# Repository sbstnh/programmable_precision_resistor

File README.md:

# Programmable Precision Resistor

A SCPI programmable precision resistor

**WARNING:** The programmable power resistor presented is mains powered. On the power supply board there will be mains/line voltage. Working with/on such devices can lead to damage, injury or death. Don't do it if you're not qualified or authorized to do so. You use the circuits described at you own risk. You have to make sure that the circuit is safe and adheres to the applicable standards in your location. You might operate the mainboard and ui board more safely with a bench or external power supply.

**WARNING:** I abandoned the AC/DC converter of the initial design mostly due to EMI issues. I ended up using a EI-core (isolation) transformer, bridge rectifier, capacitor two tiny DC/DC converters. Some of the documentation does not reflect this change.

## Background and motivation

In 2021/2022 I designed a DC electronic load that would be more capable, but also much more complex than the usual DIY solutions. However, after building a working breadboard prototype of the analog circuitry with 12 ICs including multiple precision and dual opamps, I thought that it might be better to start with a smaller project that would allow me to gain a lot of experience and write much of the non-application specific code that I could use later on for the digital part. Also, at the time I was looking for a decade resistor box to add to my lab. And this is how I started working on a programmable decade resistor, a pretty specialized tool for niche applications.

## Introduction

A programmable resistor is a electronic device whose electrical resistance can be adjusted typically through digital signals. Programmable resistors are available in form of integrated circuits (often referred to as digital potentiometers) as well as stand-alone devices/expansion cards. There are many different applications, each with their own set of requirements e. g.:

programmable gain amplifiers
sensor emulation, e. g. for integration tests with hardware-in-the-loop simulators
automated testing
calibrators
prototyping
Basic concept
The programmable resistor closely follows the main principle of resistor decade boxes: connecting multiple devices (“decades”) in series, with each of the devices having a settable resistance of 0 Ω, 1 ⋅ 10^n Ω, 2 ⋅ 10^n Ω, 9 ⋅ 10^n Ω, where n specifies the decade in question.

Those devices are simple resistor networks complemented by one (multi-throw) or more (single- or multi-throw) switches. While the actual topology and resistor values vary vastly, the switch(es) will always either short out or connect certain resistors or simply tap certain nodes of the resistor network. A simple implementation uses a 10-throw rotary switch to tap the nodes of a series resistor network of nine resistors.

## Features

| Parameter                                | Value / Description                                                                                                                                                                                                                                                                                                                                                                                                                                       |
| :--------------------------------------- | :-------------------------------------------------------------------------------------------------------------------------------------------------------------------------------------------------------------------------------------------------------------------------------------------------------------------------------------------------------------------------------------------------------------------------------------------------------- |
| Range                                    | short circuit, 1 Ω … 999.999 kΩ, open circuit                                                                                                                                                                                                                                                                                                                                                                                                          |
| Setpoint resolution                      | 1 Ω                                                                                                                                                                                                                                                                                                                                                                                                                                                      |
| Short-term setpoint accuracy estimate    | <=±0.1% of value + 0.15 Ω (2W and 4W). The estimate is based on measurements for a limited number of calibration and validation resistance setpoints. The measurements were performed with an older Agilent 34401A 6.5 digit multimeter for a single DUT. This is NOT a valid strategy to get reliable/reproducible results in the sense of a specification. It's just a more or less plausible envelope based on measurements I took for my prototype. |
| Display value resolution                 | 6.5 digits, 5.5 digits, 4.5 digits, 3.5 digits, but not better than 1 mΩ                                                                                                                                                                                                                                                                                                                                                                                 |
| Short-term display accuracy estimate     | <=±0.01% + 0.025 Ω (2W and 4W). This figure is meant to show how much the displayed resistance value (that is based on a calibration) deviates from the value shown on the DMM, the calibration has been performed with.                                                                                                                                                                                                                                |
| Thermal drift (estimate based on design) | <<50 ppm/K                                                                                                                                                                                                                                                                                                                                                                                                                                                |
| Power rating                             | >=0.2W for decade 0 (0..9Ω),<br />>=0.5W else<br />Exact value depends on setpoint (display)                                                                                                                                                                                                                                                                                                                                                             |
| Bandwidth                                | unspecified                                                                                                                                                                                                                                                                                                                                                                                                                                               |
| Calibration modes                        | - Uncalibrated: Switches are activated according to entered setpoint, display shows setpoint<br />- Two-wire (2W), Four-wire (4W): An internal setpoint is calculated based on the calibration values to reduce the error (effects changes for higher resistance values only)                                                                                                                                                                             |
| Operating modes                          | Fixed: On trigger no change<br />Step: On trigger step to trigger setpoint value<br />Up: On trigger increase setpoint (linearly, 1-2-3-4-5-6-7-8-9, 1-2-5, 1-3)<br />Down: On trigger increase setpoint (linearly, 1-2-3-4-5-6-7-8-9, 1-2-5, 1-3)<br />List: See list mode                                                                                                                                                                               |
| List mode                                | Up to 100 values with individual dwell times<br />- Start: on trigger; or immediately after mode selection<br />- Step:<br />  - Auto: Advance index automatically, solely based on dwell time<br />  - Trigger: Advance index on each trigger event, ignoring the dwell time<br />  - Once: Advance index on each trigger event, only after dwell time elapsed                                                                                           |
| Switching                                | fast (default), break-before-make                                                                                                                                                                                                                                                                                                                                                                                                                         |
| Trigger                                  | Source: Bus, External (Rising, Falling, Either), Immediate, Manual, Timer;<br />Mode: Continuous, Single<br />Parameter: Delay, Holdoff, Time (Source: Timer)                                                                                                                                                                                                                                                                                             |
| Inhibit                                  | Inhibit the input<br />- Latching: Latch input on/off on inhibit input change<br />- Live: Switch input on/off according to present inhibit input state                                                                                                                                                                                                                                                                                                   |
| Command and trigger execution            | 10ms loops                                                                                                                                                                                                                                                                                                                                                                                                                                                |
| User interface                           | - 18 digit alphanumeric display:<br />  - Primary display: Resistance setpoint<br />  - Secondary display: Input state, max. current at setpoint, max. voltage at setpoint, max. power at setpoint, hardware setpoint<br />  - Menu-based<br />- 6 dual color LEDs<br />- Rotary encoder with push button<br />- 23 additional push buttons                                                                                                               |
| User presets                             | 0-9; 0 is loaded on power-up                                                                                                                                                                                                                                                                                                                                                                                                                              |
| Interface                                | - USB<br />- Two digital inputs, settable polarity (positive, negative) and function (trigger, inhibit, readout)                                                                                                                                                                                                                                                                                                                                          |
| Power supply                             | Switch mode                                                                                                                                                                                                                                                                                                                                                                                                                                               |

## System design

The block diagram provides an overview of the different circuit groups of each functional block, their internal connections and external interfaces. The Programmable Decade Resistor consists of three main functional blocks:

1. Power supply (Power Supply Board), an external EMI filter is required.
2. Programmable decades, control and driver circuits (Mainboard)
3. User Interface (User Interface Board)

The power supply board uses an off-the-shelve AC/DC converter to provide a +15V rail. The +15V rail powers the relays on the mainboard as well as a DC/DC converter. A single DC/DC converter generates a +3.3V supply for both the mainboard and the UI board, including the LED display. The power rails are earth-referenced. (Nevertheless, the inputs of the Programmable Decade Resistor are floating thanks to the isolation of the relays.)

The mainboard’s main controller contains the business logic to control the relays, read the external inputs and run the USB and user interfaces. The main controller communicates with the User Interface Board over I2C which handles the multiplexing of the alphanumeric LED display, scans the switch matrix, decodes the signals of the rotary encoder and drives the buzzer.

Note that these pictures DO NOT represent the final design of the Programmable Precision Resistor and the power supply circuit in particular.

## Results

After the final calibration the results are in. The first diagram shows the absolute value of the deviation between the setpoint and the value indicated by the Agilent 34401A multimeter. Connecting lines between data points for visual purposes only.

The second diagram shows the absolute value of the deviation between the calculated resistance (estimate based on calibration values) and the value indicated by the Agilent 34401A multimeter. Connecting lines between data points for visual purposes only

## About this repository

This repository contains the PCB design files used in this project. If you'd like to have a look at the interactive bom files you can do so here:

- Mainboard: [HTML Preview of interactive BOM](https://htmlpreview.github.io/?https://github.com/sbstnh/programmable_precision_resistor/blob/main/pcb/mainboard/bom/ibom.html)
- UI board: [HTML Preview of interactive BOM](https://htmlpreview.github.io/?https://github.com/sbstnh/programmable_precision_resistor/blob/main/pcb/ui_board/bom/ibom.html)
- Power Supply Board: [HTML Preview of interactive BOM](https://htmlpreview.github.io/?https://github.com/sbstnh/programmable_precision_resistor/blob/main/pcb/power_supply/bom/ibom.html)

## Further information

More details are available at [https://hackaday.io/project/191969-programmable-precision-resistor](https://hackaday.io/project/191969-programmable-precision-resistor) and on my personal site [https://sebastianharnisch.de](https://sebastianharnisch.de).

## Firmware and License

The firmware was created with STM32CubeIDE and uses code auto-generated by or provided with the IDE, including
- the HAL library, code related to the USB device and other code
- FreeRTOS

Further more, this project uses a SCPI parser library that can be found here: [https://github.com/j123b567/scpi-parser](https://github.com/j123b567/scpi-parser)

Most of the auto-generated code as well as the libraries are not included here.
Therefore it is recommended to use STM32CubeIDE to create a project for the target device, with the USB device software and FreeRTOS enabled, add the required SCPI library and adapt the code according to the requirements.

For the code not included in this repository the respective licenses will apply instead of the license specified in this repository.

I DO NOT guarantee that the code provided is free of bugs (see LICENSE file for more details).

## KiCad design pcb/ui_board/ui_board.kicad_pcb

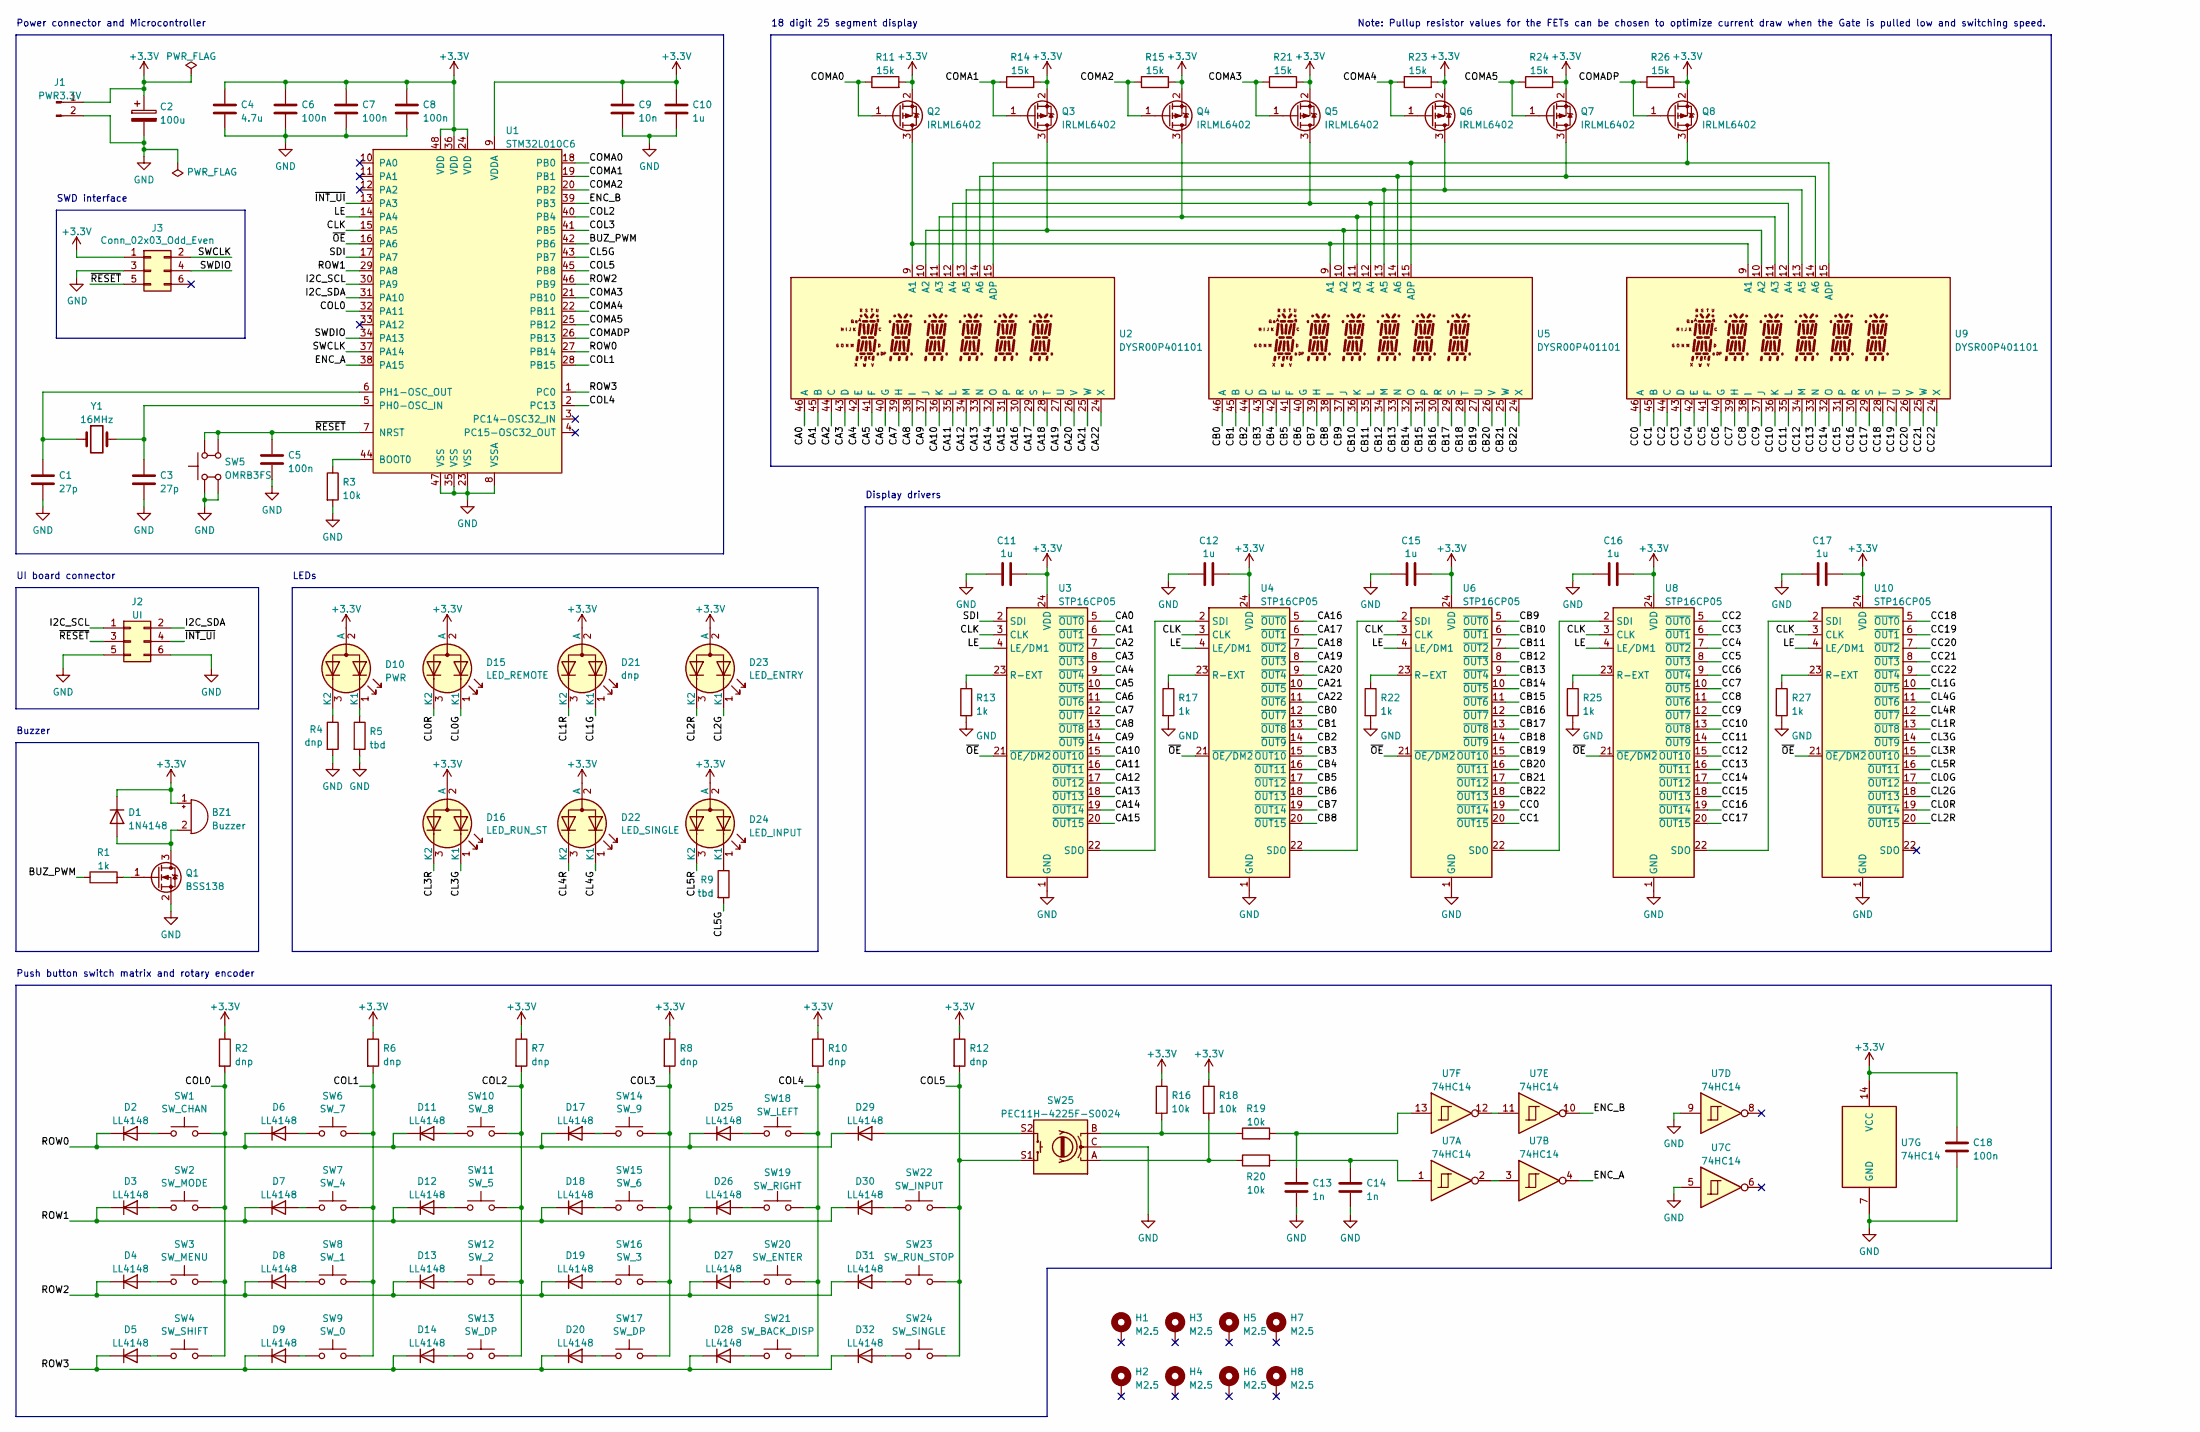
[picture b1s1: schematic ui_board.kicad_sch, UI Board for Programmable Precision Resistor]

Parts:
BZ1: Buzzer; Buzzer_Ekulit_AL-60P06_D12mm_H9mm
C1, C3: 27p; C_0603_1608Metric_Box
C2: 100u; CP_EIA-7343-31_Kemet-D_Pad2.25x2.55mm_HandSolder
C4: 4.7u; C_0603_1608Metric_Box
C5, C6, C7, C8, C18: 100n; C_0603_1608Metric_Box
C9: 10n; C_0603_1608Metric_Box
C10, C11, C12, C15, C16, C17: 1u; C_0603_1608Metric_Box
C13, C14: 1n; C_0603_1608Metric_Box
D1: 1N4148; D_MiniMELF
D2, D3, D4, D5, D6, D7, D8, D9, D11, D12, D13, D14, D17, D18, D19, D20, D25, D26, D27, D28, D29, D30, D31, D32: LL4148; D_MiniMELF
D10: PWR; LED_D3.0mm-3
D15: LED_REMOTE; LED_D3.0mm-3
D16: LED_RUN_ST; LED_D3.0mm-3
D21: dnp; LED_D3.0mm-3
D22: LED_SINGLE; LED_D3.0mm-3
D23: LED_ENTRY; LED_D3.0mm-3
D24: LED_INPUT; LED_D3.0mm-3
H1, H2, H3, H4, H5, H6, H7, H8: M2.5; MountingHole_2.7mm_M2.5_DIN965_Pad
J1: PWR3.3V; Molex_KK-254_AE-6410-02A_1x02_P2.54mm_Vertical
J2: UI; PinHeader_2x03_P2.54mm_Vertical
J3: Conn_02x03_Odd_Even; PinHeader_2x03_P2.54mm_Vertical
Q1: BSS138; SOT-23
Q2, Q3, Q4, Q5, Q6, Q7, Q8: IRLML6402; SOT-23
R1: 1k; R_0805_2012Metric_Box
R2, R4, R6, R7, R8, R10, R12: dnp; R_0603_1608Metric_Box
R3, R16, R18, R19, R20: 10k; R_0603_1608Metric_Box
R5, R9: tbd; R_0603_1608Metric_Box
R11, R14, R15, R21, R23, R24, R26: 15k; R_0603_1608Metric_Box
R13, R17, R22, R25, R27: 1k; R_0603_1608Metric_Box
SW1: SW_CHAN; PVA1
SW2: SW_MODE; PVA1
SW3: SW_MENU; PVA1
SW4: SW_SHIFT; PVA1
SW5: OMRB3FS; OMR_B3FS
SW6: SW_7; PVA1
SW7: SW_4; PVA1
SW8: SW_1; PVA1
SW9: SW_0; PVA1
SW10: SW_8; PVA1
SW11: SW_5; PVA1
SW12: SW_2; PVA1
SW13, SW17: SW_DP; PVA1
SW14: SW_9; PVA1
SW15: SW_6; PVA1
SW16: SW_3; PVA1
SW18: SW_LEFT; PVA1
SW19: SW_RIGHT; PVA1
SW20: SW_ENTER; PVA1
SW21: SW_BACK_DISP; PVA1
SW22: SW_INPUT; PVA1
SW23: SW_RUN_STOP; PVA1
SW24: SW_SINGLE; PVA1
SW25: PEC11H-4225F-S0024; RotaryEncoder_Alps_EC11E-Switch_Vertical_H20mm_CircularMoun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
U1: STM32L010C6; LQFP-48_7x7mm_P0.5mm
U2, U5, U9: DYSR00P401101
U3, U4, U6, U8, U10: STP16CP05; TSSOP-24_4.4x7.8mm_P0.65mm
U7: 74HC14; SO-14_3.9x8.65mm_P1.27mm
Y1: 16MHz; Crystal_HC49-4H_Vertical

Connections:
+3.3V: BZ1.1 (-), C2.1, C4.1, C6.1, C7.1, C8.1, C9.1, C10.1, C11.1, C12.1, C15.1, C16.1, C17.1, C18.1, D1.1 (K), D10.2 (A), D15.2 (A), D16.2 (A), D21.2 (A), D22.2 (A), D23.2 (A), D24.2 (A), J1.1, J3.1, Q2.2 (S), Q3.2 (S), Q4.2 (S), Q5.2 (S), Q6.2 (S), Q7.2 (S), Q8.2 (S), R2.1, R6.1, R7.1, R8.1, R10.1, R11.2, R12.1, R14.2, R15.2, R16.1, R18.1, R21.2, R23.2, R24.2, R26.2, U1.9 (VDDA), U1.24 (VDD), U1.36 (VDD), U1.48 (VDD), U3.24 (VDD), U4.24 (VDD), U6.24 (VDD), U7.14 (VCC), U8.24 (VDD), U10.24 (VDD)
/BUZ_PWM: R1.1, U1.42 (PB6)
/CA0: U2.46 (A), U3.5 (~OUT0)
/CA1: U2.45 (B), U3.6 (~OUT1)
/CA2: U2.44 (C), U3.7 (~OUT2)
/CA3: U2.43 (D), U3.8 (~OUT3)
/CA4: U2.42 (E), U3.9 (~OUT4)
/CA5: U2.41 (F), U3.10 (~OUT5)
/CA6: U2.40 (G), U3.11 (~OUT6)
/CA7: U2.39 (H), U3.12 (~OUT7)
/CA8: U2.38 (I), U3.13 (~OUT8)
/CA9: U2.37 (J), U3.14 (~OUT9)
/CA10: U2.36 (K), U3.15 (~OUT10)
/CA11: U2.35 (L), U3.16 (~OUT11)
/CA12: U2.34 (M), U3.17 (~OUT12)
/CA13: U2.33 (N), U3.18 (~OUT13)
/CA14: U2.32 (O), U3.19 (~OUT14)
/CA15: U2.31, U3.20 (~OUT15)
/CA16: U2.30 (R), U4.5 (~OUT0)
/CA17: U2.29 (S), U4.6 (~OUT1)
/CA18: U2.28 (T), U4.7 (~OUT2)
/CA19: U2.27 (U), U4.8 (~OUT3)
/CA20: U2.26 (V), U4.9 (~OUT4)
/CA21: U2.25 (W), U4.10 (~OUT5)
/CA22: U2.24 (X), U4.11 (~OUT6)
/CB0: U4.12 (~OUT7), U5.46 (A)
/CB1: U4.13 (~OUT8), U5.45 (B)
/CB2: U4.14 (~OUT9), U5.44 (C)
/CB3: U4.15 (~OUT10), U5.43 (D)
/CB4: U4.16 (~OUT11), U5.42 (E)
/CB5: U4.17 (~OUT12), U5.41 (F)
/CB6: U4.18 (~OUT13), U5.40 (G)
/CB7: U4.19 (~OUT14), U5.39 (H)
/CB8: U4.20 (~OUT15), U5.38 (I)
/CB9: U5.37 (J), U6.5 (~OUT0)
/CB10: U5.36 (K), U6.6 (~OUT1)
/CB11: U5.35 (L), U6.7 (~OUT2)
/CB12: U5.34 (M), U6.8 (~OUT3)
/CB13: U5.33 (N), U6.9 (~OUT4)
/CB14: U5.32 (O), U6.10 (~OUT5)
/CB15: U5.31, U6.11 (~OUT6)
/CB16: U5.30 (R), U6.12 (~OUT7)
/CB17: U5.29 (S), U6.13 (~OUT8)
/CB18: U5.28 (T), U6.14 (~OUT9)
/CB19: U5.27 (U), U6.15 (~OUT10)
/CB20: U5.26 (V), U6.16 (~OUT11)
/CB21: U5.25 (W), U6.17 (~OUT12)
/CB22: U5.24 (X), U6.18 (~OUT13)
/CC0: U6.19 (~OUT14), U9.46 (A)
/CC1: U6.20 (~OUT15), U9.45 (B)
/CC2: U8.5 (~OUT0), U9.44 (C)
/CC3: U8.6 (~OUT1), U9.43 (D)
/CC4: U8.7 (~OUT2), U9.42 (E)
/CC5: U8.8 (~OUT3), U9.41 (F)
/CC6: U8.9 (~OUT4), U9.40 (G)
/CC7: U8.10 (~OUT5), U9.39 (H)
/CC8: U8.11 (~OUT6), U9.38 (I)
/CC9: U8.12 (~OUT7), U9.37 (J)
/CC10: U8.13 (~OUT8), U9.36 (K)
/CC11: U8.14 (~OUT9), U9.35 (L)
/CC12: U8.15 (~OUT10), U9.34 (M)
/CC13: U8.16 (~OUT11), U9.33 (N)
/CC14: U8.17 (~OUT12), U9.32 (O)
/CC15: U8.18 (~OUT13), U9.31
/CC16: U8.19 (~OUT14), U9.30 (R)
/CC17: U8.20 (~OUT15), U9.29 (S)
/CC18: U9.28 (T), U10.5 (~OUT0)
/CC19: U9.27 (U), U10.6 (~OUT1)
/CC20: U9.26 (V), U10.7 (~OUT2)
/CC21: U9.25 (W), U10.8 (~OUT3)
/CC22: U9.24 (X), U10.9 (~OUT4)
/CL0G: D15.1 (K1), U10.17 (~OUT12)
/CL0R: D15.3 (K2), U10.19 (~OUT14)
/CL1G: D21.1 (K1), U10.10 (~OUT5)
/CL1R: D21.3 (K2), U10.13 (~OUT8)
/CL2G: D23.1 (K1), U10.18 (~OUT13)
/CL2R: D23.3 (K2), U10.20 (~OUT15)
/CL3G: D16.1 (K1), U10.14 (~OUT9)
/CL3R: D16.3 (K2), U10.15 (~OUT10)
/CL4G: D22.1 (K1), U10.11 (~OUT6)
/CL4R: D22.3 (K2), U10.12 (~OUT7)
/CL5G: R9.2, U1.43 (PB7)
/CL5R: D24.3 (K2), U10.16 (~OUT11)
/CLK: U1.15 (PA5), U3.3 (CLK), U4.3 (CLK), U6.3 (CLK), U8.3 (CLK), U10.3 (CLK)
/COL0: R2.2, SW1.2, SW2.2, SW3.2, SW4.2, U1.32 (PA11)
/COL1: R6.2, SW6.2, SW7.2, SW8.2, SW9.2, U1.28 (PB15)
/COL2: R7.2, SW10.2, SW11.2, SW12.2, SW13.2, U1.40 (PB4)
/COL3: R8.2, SW14.2, SW15.2, SW16.2, SW17.2, U1.41 (PB5)
/COL4: R10.2, SW18.2, SW19.2, SW20.2, SW21.2, U1.2 (PC13)
/COL5: R12.2, SW22.2, SW23.2, SW24.2, SW25.S1, U1.45 (PB8)
/COMA0: Q2.1 (G), R11.1, U1.18 (PB0)
/COMA1: Q3.1 (G), R14.1, U1.19 (PB1)
/COMA2: Q4.1 (G), R15.1, U1.20 (PB2)
/COMA3: Q5.1 (G), R21.1, U1.21 (PB10)
/COMA4: Q6.1 (G), R23.1, U1.22 (PB11)
/COMA5: Q7.1 (G), R24.1, U1.25 (PB12)
/COMADP: Q8.1 (G), R26.1, U1.26 (PB13)
/ENC_A: U1.38 (PA15), U7.4
/ENC_B: U1.39 (PB3), U7.10
/I2C_SCL: J2.1, U1.30 (PA9)
/I2C_SDA: J2.2, U1.31 (PA10)
/LE: U1.14 (PA4), U3.4 (LE/DM1), U4.4 (LE/DM1), U6.4 (LE/DM1), U8.4 (LE/DM1), U10.4 (LE/DM1)
/ROW0: D2.1 (K), D6.1 (K), D11.1 (K), D17.1 (K), D25.1 (K), D29.1 (K), U1.27 (PB14)
/ROW1: D3.1 (K), D7.1 (K), D12.1 (K), D18.1 (K), D26.1 (K), D30.1 (K), U1.29 (PA8)
/ROW2: D4.1 (K), D8.1 (K), D13.1 (K), D19.1 (K), D27.1 (K), D31.1 (K), U1.46 (PB9)
/ROW3: D5.1 (K), D9.1 (K), D14.1 (K), D20.1 (K), D28.1 (K), D32.1 (K), U1.1 (PC0)
/SDI: U1.17 (PA7), U3.2 (SDI)
/SWCLK: J3.2, U1.37 (PA14)
/SWDIO: J3.4, U1.34 (PA13)
/~INT_UI: J2.4, U1.13 (PA3)
/~OE: U1.16 (PA6), U3.21 (~OE/DM2), U4.21 (~OE/DM2), U6.21 (~OE/DM2), U8.21 (~OE/DM2), U10.21 (~OE/DM2)
/~RESET: C5.1, J2.3, J3.5, SW5.3, SW5.4, U1.7 (NRST)
GND: C1.2, C2.2, C3.2, C4.2, C5.2, C6.2, C7.2, C8.2, C9.2, C10.2, C11.2, C12.2, C13.2, C14.2, C15.2, C16.2, C17.2, C18.2, J1.2, J2.5, J2.6, J3.3, Q1.2 (S), R3.2, R4.2, R5.2, R13.2, R17.2, R22.2, R25.2, R27.2, SW5.1, SW5.2, SW25.C, U1.8 (VSSA), U1.23 (VSS), U1.35 (VSS), U1.47 (VSS), U3.1 (GND), U4.1 (GND), U6.1 (GND), U7.5, U7.7 (GND), U7.9, U8.1 (GND), U10.1 (GND)
unnamed: BZ1.2 (+), D1.2 (A), Q1.3 (D)
unnamed: C13.1, R19.2, U7.13
unnamed: C14.1, R20.2, U7.1
unnamed: D2.2 (A), SW1.1
unnamed: D3.2 (A), SW2.1
unnamed: D4.2 (A), SW3.1
unnamed: D5.2 (A), SW4.1
unnamed: D6.2 (A), SW6.1
unnamed: D7.2 (A), SW7.1
unnamed: D8.2 (A), SW8.1
unnamed: D9.2 (A), SW9.1
unnamed: D10.1 (K1), R5.1
unnamed: D10.3 (K2), R4.1
unnamed: D11.2 (A), SW10.1
unnamed: D12.2 (A), SW11.1
unnamed: D13.2 (A), SW12.1
unnamed: D14.2 (A), SW13.1
unnamed: D17.2 (A), SW14.1
unnamed: D18.2 (A), SW15.1
unnamed: D19.2 (A), SW16.1
unnamed: D20.2 (A), SW17.1
unnamed: D24.1 (K1), R9.1
unnamed: D25.2 (A), SW18.1
unnamed: D26.2 (A), SW19.1
unnamed: D27.2 (A), SW20.1
unnamed: D28.2 (A), SW21.1
unnamed: D29.2 (A), SW25.S2
unnamed: D30.2 (A), SW22.1
unnamed: D31.2 (A), SW23.1
unnamed: D32.2 (A), SW24.1
unnamed: Q1.1 (G), R1.2
unnamed: Q2.3 (D), U2.9 (A1), U5.9 (A1), U9.9 (A1)
unnamed: Q3.3 (D), U2.10 (A2), U5.10 (A2), U9.10 (A2)
unnamed: Q4.3 (D), U2.11 (A3), U5.11 (A3), U9.11 (A3)
unnamed: Q5.3 (D), U2.12 (A4), U5.12 (A4), U9.12 (A4)
unnamed: Q6.3 (D), U2.13 (A5), U5.13 (A5), U9.13 (A5)
unnamed: Q7.3 (D), U2.14 (A6), U5.14 (A6), U9.14 (A6)
unnamed: Q8.3 (D), U2.15 (ADP), U5.15 (ADP), U9.15 (ADP)
unnamed: R16.2, R19.1, SW25.B
unnamed: R18.2, R20.1, SW25.A
unnamed: R3.1, U1.44 (BOOT0)
unnamed: C3.1, U1.5 (PH0-OSC_IN), Y1.2
unnamed: C1.1, U1.6 (PH1-OSC_OUT), Y1.1
unnamed: R13.1, U3.23 (R-EXT)
unnamed: U3.22 (SDO), U4.2 (SDI)
unnamed: R17.1, U4.23 (R-EXT)
unnamed: U4.22 (SDO), U6.2 (SDI)
unnamed: R22.1, U6.23 (R-EXT)
unnamed: U6.22 (SDO), U8.2 (SDI)
unnamed: U7.2, U7.3
unnamed: U7.11, U7.12
unnamed: R25.1, U8.23 (R-EXT)
unnamed: R27.1, U10.23 (R-EXT)
unnamed: U8.22 (SDO), U10.2 (SDI)

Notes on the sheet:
Push button switch matrix and rotary encoder
Display drivers
18 digit 25 segment display
SWD interface
LEDs
Power connector and Microcontroller
UI board connector
Buzzer
Note: Pullup resistor values for the FETs can be chosen to optimize current draw when the Gate is pulled low and switching speed.

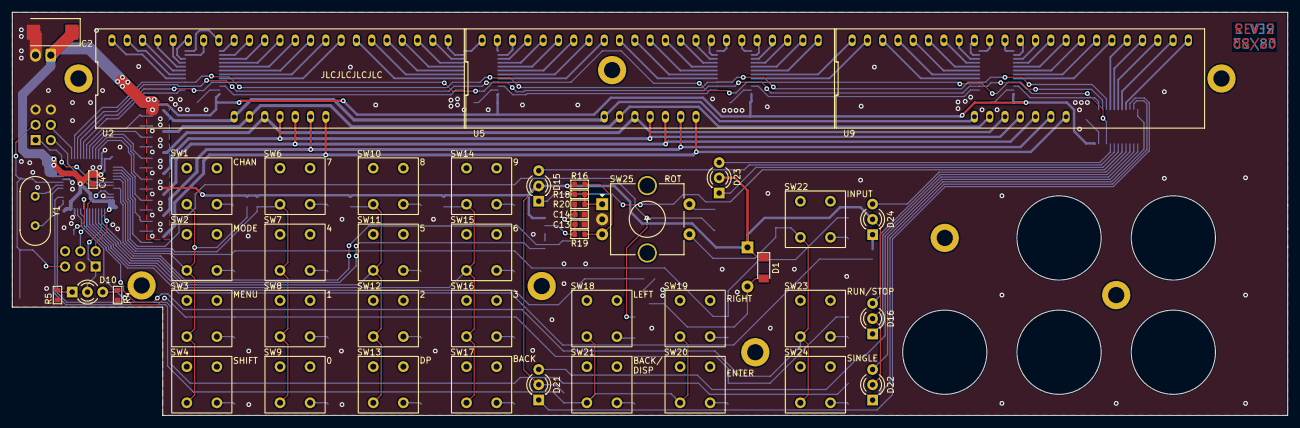
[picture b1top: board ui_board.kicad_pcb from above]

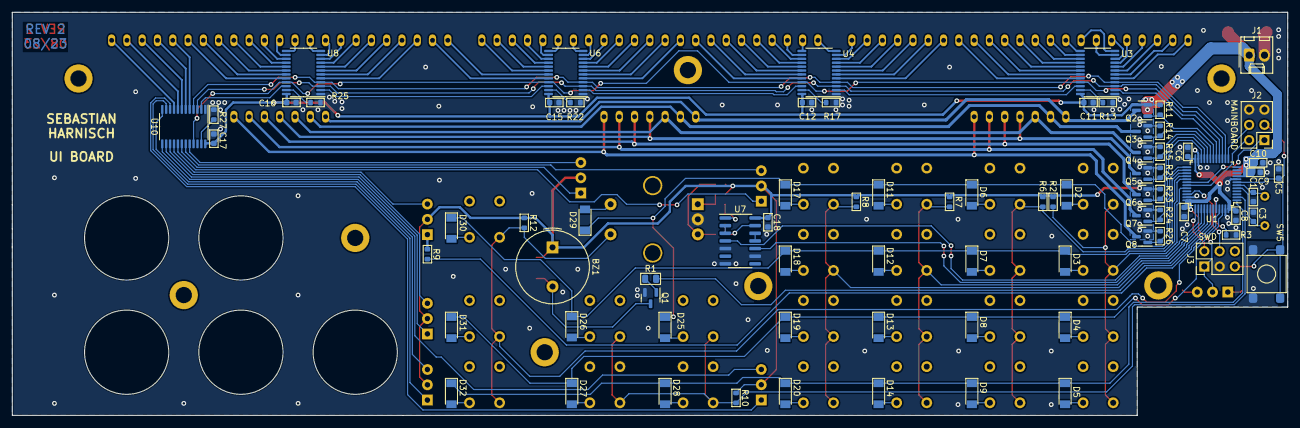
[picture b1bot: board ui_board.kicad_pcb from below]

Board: 2 copper layers, 212.0 x 67.0 mm, 133 parts (79 on the bottom side), 167 nets.

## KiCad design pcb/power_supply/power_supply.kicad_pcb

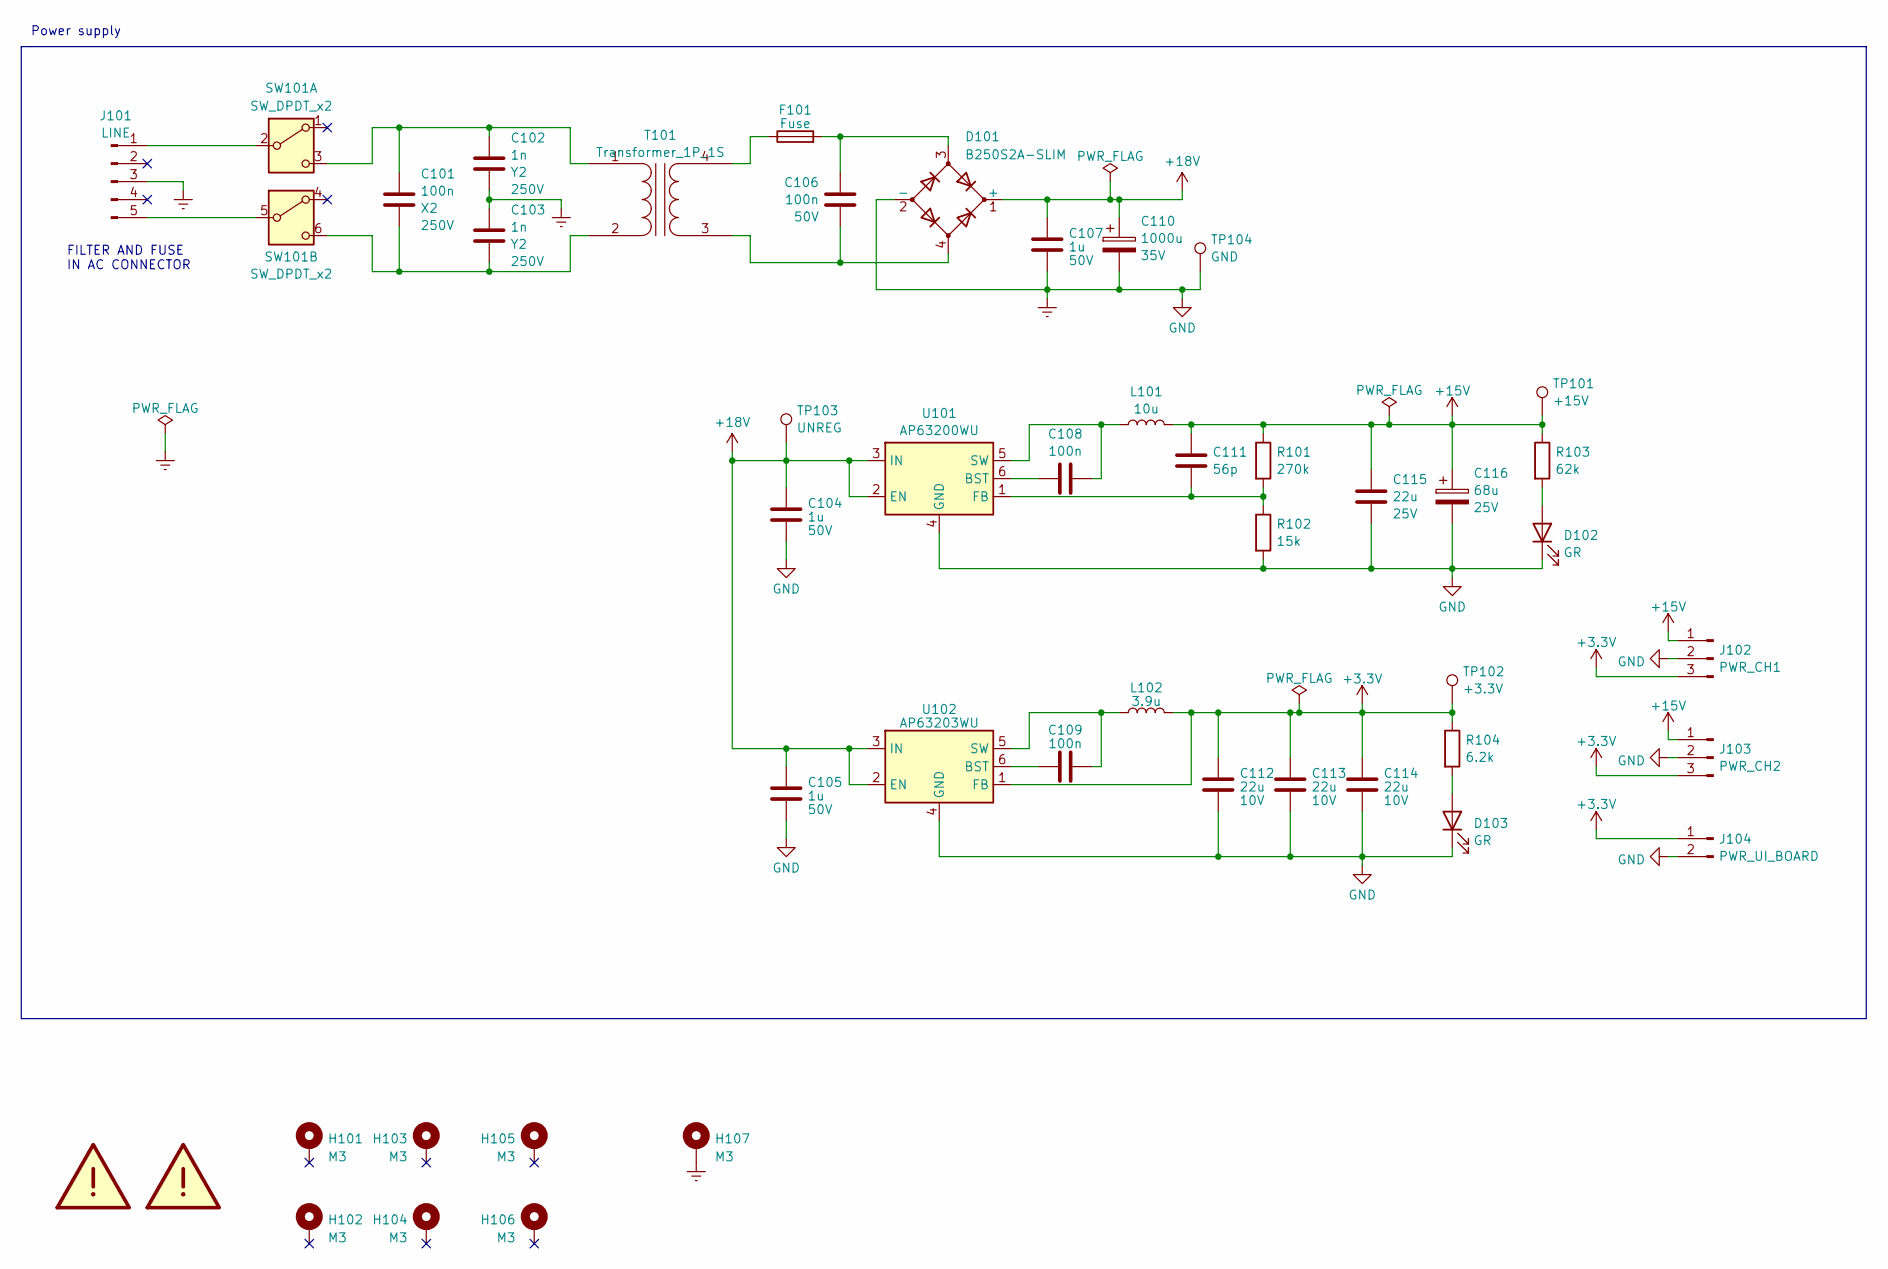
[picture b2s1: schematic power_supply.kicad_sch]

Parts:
C101: 100n; C_Rect_L18.0mm_W5.0mm_P15.00mm_FKS3_FKP3; Voltage Rating 250V
C102, C103: 1n; C_Rect_L13.5mm_W5.0mm_P10.00mm_FKS3_FKP3_MKS4; Voltage Rating 250V
C104, C105: 1u; C_1206_3216Metric; Voltage Rating 50V
C106: 100n; C_0805_2012Metric; Voltage Rating 50V
C107: 1u; C_0805_2012Metric; Voltage Rating 50V
C108, C109: 100n; C_0603_1608Metric
C110: 1000u; CP_Radial_D16.0mm_P7.50mm; Voltage Rating 35V
C111: 56p; C_0603_1608Metric
C112, C113, C114: 22u; C_1206_3216Metric; Voltage Rating 10V
C115: 22u; C_1206_3216Metric; Voltage Rating 25V
C116: 68u; C_Elec_6.3x5.8; Voltage Rating 25V
D101: B250S2A-SLIM; Diode_Bridge_Diotec_SO-DIL-Slim
D102, D103: GR; LED_0603_1608Metric
F101: Fuse; Fuse_1206_3216Metric
H101, H102, H103, H104, H105, H106: M3; MountingHole_3.2mm_M3_DIN965_Pad
H107: M3; MountingHole_2.2mm_M2_DIN965_Pad
J101: LINE; Molex_KK-396_A-41791-0005_1x05_P3.96mm_Vertical
J102: PWR_CH1; Molex_KK-254_AE-6410-03A_1x03_P2.54mm_Vertical
J103: PWR_CH2; Molex_KK-254_AE-6410-03A_1x03_P2.54mm_Vertical
J104: PWR_UI_BOARD; Molex_KK-254_AE-6410-02A_1x02_P2.54mm_Vertical
L101: 10u; L_Bourns-SRN4018
L102: 3.9u; L_Bourns-SRN4018
LOGO101, LOGO102: SYMBOL_TRIANGLE_WARNING; Triangle_Warning
R101: 270k; R_0603_1608Metric
R102: 15k; R_0603_1608Metric
R103: 62k; R_0603_1608Metric
R104: 6.2k; R_0603_1608Metric
SW101: SW_DPDT_x2; NE1848EE
T101: Transformer_1P_1S; BLOCK_VC16_1
TP101: +15V; TestPoint_Keystone_5000-5004_Miniature
TP102: +3.3V; TestPoint_Keystone_5000-5004_Miniature
TP103: UNREG; TestPoint_Keystone_5000-5004_Miniature
TP104: GND; TestPoint_Keystone_5000-5004_Miniature
U101: AP63200WU; TSOT-23-6
U102: AP63203WU; TSOT-23-6

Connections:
+3.3V: C112.1, C113.1, C114.1, J102.3, J103.3, J104.1, L102.2, R104.1, TP102.1, U102.1 (FB)
+15V: C111.2, C115.1, C116.1, J102.1, J103.1, L101.2, R101.1, R103.1, TP101.1
+18V: C104.1, C105.1, C107.1, C110.1, D101.1 (+), TP103.1, U101.2 (EN), U101.3 (IN), U102.2 (EN), U102.3 (IN)
Earth: C102.2, C103.1, C104.2, C105.2, C107.2, C110.2, C112.2, C113.2, C114.2, C115.2, C116.2, D101.2 (-), D102.1 (K), D103.1 (K), H107.1, J101.3, J102.2, J103.2, J104.2, R102.2, TP104.1, U101.4 (GND), U102.4 (GND)
unnamed: C106.1, D101.3, F101.2
unnamed: D102.2 (A), R103.2
unnamed: D103.2 (A), R104.2
unnamed: J101.1, SW101.2 (B)
unnamed: J101.5, SW101.5 (B)
unnamed: C101.1, C102.1, SW101.3 (C), T101.1 (AA)
unnamed: C101.2, C103.2, SW101.6 (C), T101.2 (AB)
unnamed: C106.2, D101.4, T101.3 (SA)
unnamed: F101.1, T101.4 (SB)
unnamed: C108.1, U101.6 (BST)
unnamed: C111.1, R101.2, R102.1, U101.1 (FB)
unnamed: C108.2, L101.1, U101.5 (SW)
unnamed: C109.1, U102.6 (BST)
unnamed: C109.2, L102.1, U102.5 (SW)

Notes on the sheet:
Power supply
FILTER AND FUSE IN AC CONNECTOR

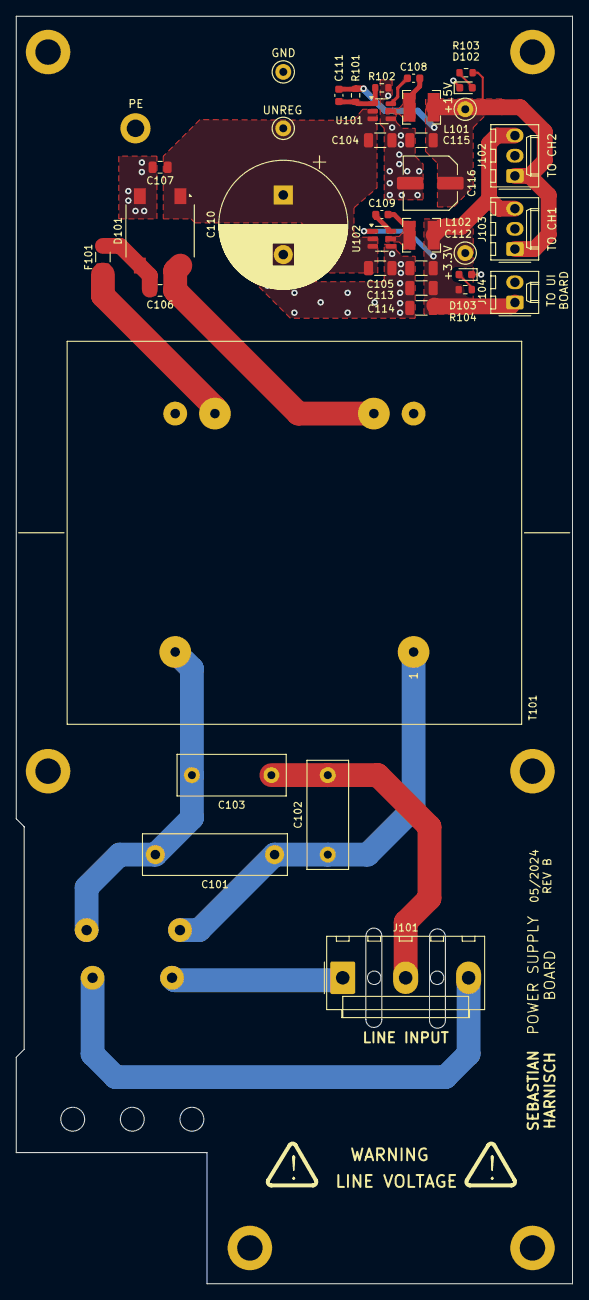
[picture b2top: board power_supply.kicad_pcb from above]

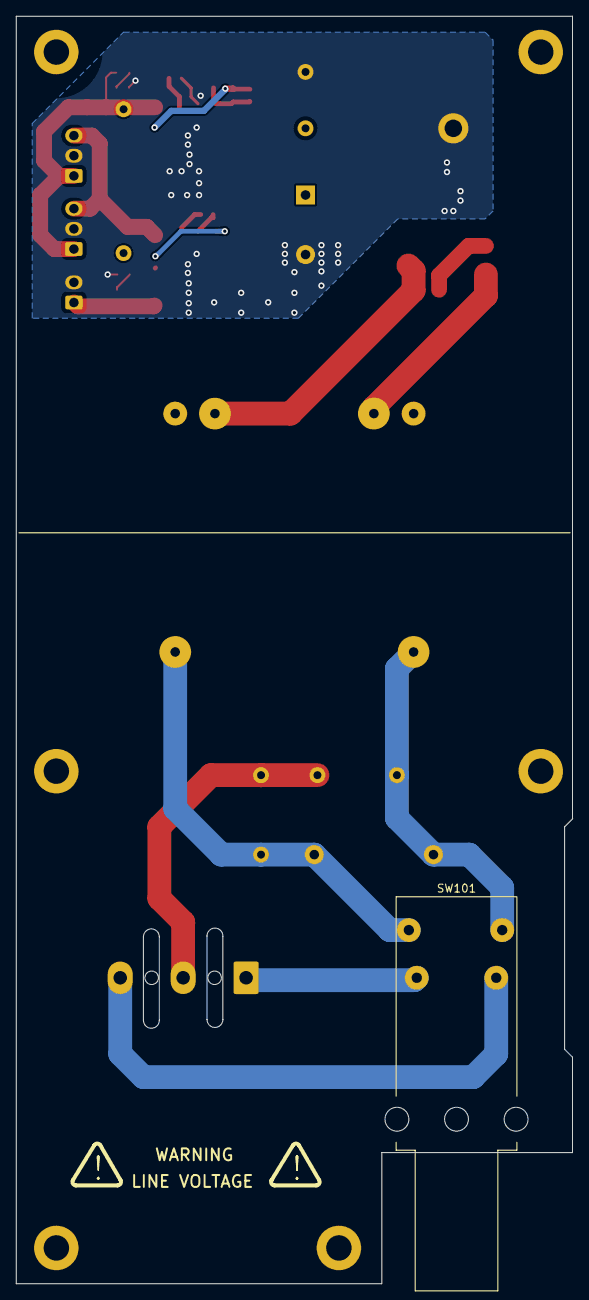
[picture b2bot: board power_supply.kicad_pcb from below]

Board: 2 copper layers, 70.0 x 159.5 mm, 49 parts (3 on the bottom side), 18 nets.

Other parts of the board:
LOGO101#2, LOGO101#3: SYMBOL_TRIANGLE_WARNING; Triangle_Warning

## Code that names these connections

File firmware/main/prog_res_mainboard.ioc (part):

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Mcu.Name=STM32G441KBTx
Mcu.Package=LQFP32
Mcu.UserName=STM32G441KBTx
PA11.Mode=Device
PA11.Signal=USB_DM
PA12.Mode=Device
PA12.Signal=USB_DP
PA13.Mode=Serial_Wire
PA13.Signal=SYS_JTMS-SWDIO
PA14.Mode=Serial_Wire
PA14.Signal=SYS_JTCK-SWCLK
PA15.Mode=I2C
PA15.Signal=I2C1_SCL
PA2.GPIOParameters=GPIO_Label
PA2.GPIO_Label=RLY_PWR
PA2.Signal=GPIO_Output
PA3.GPIOParameters=GPIO_Label
PA3.GPIO_Label=ADC1_IN4_TEMP1
PA3.Mode=IN4-Single-Ended
PA3.Signal=ADC1_IN4
PA4.GPIOParameters=GPIO_Label
PA4.GPIO_Label=RLY_LE
PA4.Signal=GPIO_Output
PA5.GPIOParameters=GPIO_Label
PA5.GPIO_Label=RLY_SPI1_SCK
PA5.Mode=TX_Only_Simplex_Unidirect_Master
PA5.Signal=SPI1_SCK
PA6.GPIOParameters=GPIO_Label
PA6.GPIO_Label=RLY_OE
PA6.Signal=GPIO_Output
PA7.GPIOParameters=GPIO_Label
PA7.GPIO_Label=RLY_SPI1_MOSI
PA7.Mode=TX_Only_Simplex_Unidirect_Master
PA7.Signal=SPI1_MOSI
PA8.GPIOParameters=GPIO_Label
PA8.GPIO_Label=GPIO_EXT_IN2
PA8.Signal=GPIO_Input
PA9.GPIOParameters=GPIO_Label
PA9.GPIO_Label=GPIO_EXT_IN1
PA9.Signal=GPIO_Input
PB0.GPIOParameters=GPIO_Label
PB0.GPIO_Label=ADC1_IN_15_TEMP2
PB0.Mode=IN15-Single-Ended
PB0.Signal=ADC1_IN15
PB3.GPIOParameters=GPIO_Label
PB3.GPIO_Label=NC
PB3.Signal=GPIO_Input
PB4.GPIOParameters=GPIO_Label
PB4.GPIO_Label=INT_UI
PB4.Signal=GPIO_Input
PB7.Mode=I2C
PB7.Signal=I2C1_SDA
PF0-OSC_IN.Mode=HSE-External-Oscillator
PF0-OSC_IN.Signal=RCC_OSC_IN
PF1-OSC_OUT.Mode=HSE-External-Oscillator
PF1-OSC_OUT.Signal=RCC_OSC_OUT
RCC.HSE_VALUE=16000000
RCC.SYSCLKFreq_VALUE=160000000
RCC.SYSCLKSource=RCC_SYSCLKSOURCE_PLLCLK
board=custom
